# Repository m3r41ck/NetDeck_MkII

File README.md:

# Custom Macropad Project

## Project Overview
This is a custom macropad I designed, assembled, and programmed as a personal project to strengthen my hardware and embedded systems skills.

## Features
- PCB design (created using KiCad)
- Firmware flashing QMK
- Hardware assembly and soldering

## Current Status
✅ Moved from breadboard to custom PCB.  
🔜 Designing custom enclosure and expanding firmware functionality.

## Lessons Learned
- Double-check PCB traces before ordering!
- How to debug hardware connections
- How to flash and customize firmware

## Next Steps
- Design and 3D-print an enclosure
- Add support for additional macros and features

## Images

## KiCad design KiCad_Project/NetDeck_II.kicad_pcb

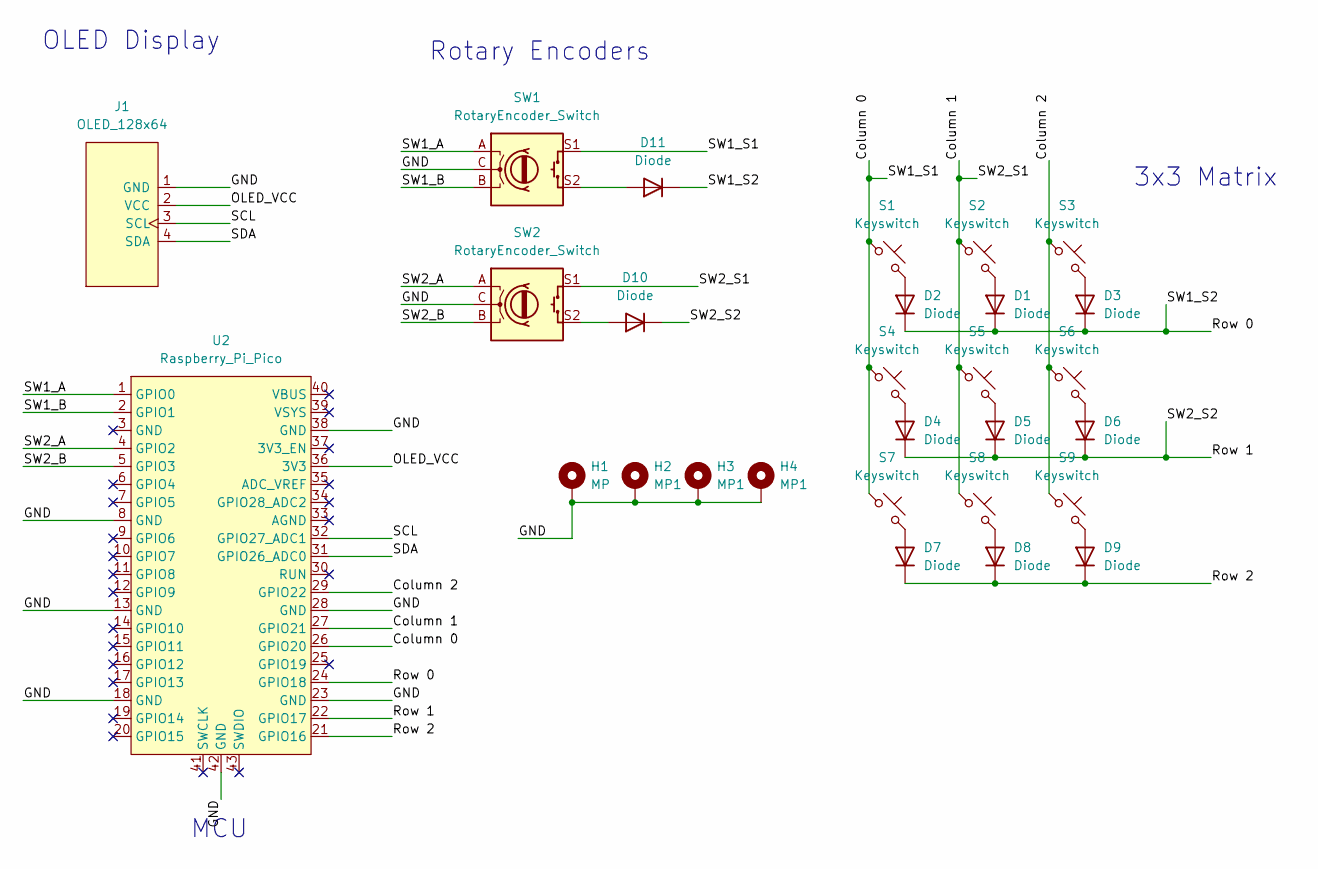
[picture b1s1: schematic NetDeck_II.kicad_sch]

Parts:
D1, D2, D3, D4, D5, D6, D7, D8, D9, D10, D11: Diode; Diode_DO-35
H1: MP; MountingHole_3.5mm_Pad_Via
H2, H3, H4: MP1; MountingHole_3.5mm_Pad_Via
J1: OLED_128x64
S1, S2, S3, S4, S5, S6, S7, S8, S9: Keyswitch; MX_PCB_1.00u
SW1, SW2: RotaryEncoder_Switch; RotaryEncoder_Alps_EC11E-Switch_Vertical_H20mm
U2: Raspberry_Pi_Pico

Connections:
/Column 0: S1.1, S4.1, S7.1, SW1.S1, U2.26 (GPIO20)
/Column 1: S2.1, S5.1, S8.1, SW2.S1, U2.27 (GPIO21)
/Column 2: S3.1, S6.1, S9.1, U2.29 (GPIO22)
/GND: H1.1, H2.1, H3.1, H4.1, J1.1 (GND), SW1.C, SW2.C, U2.8 (GND), U2.13 (GND), U2.18 (GND), U2.23 (GND), U2.28 (GND), U2.38 (GND), U2.42 (GND)
/OLED_VCC: J1.2 (VCC), U2.36 (3V3)
/Row 0: D1.1 (K), D2.1 (K), D3.1 (K), D11.1 (K), U2.24 (GPIO18)
/Row 1: D4.1 (K), D5.1 (K), D6.1 (K), D10.1 (K), U2.22 (GPIO17)
/Row 2: D7.1 (K), D8.1 (K), D9.1 (K), U2.21 (GPIO16)
/SCL: J1.3 (SCL), U2.32 (GPIO27_ADC1)
/SDA: J1.4 (SDA), U2.31 (GPIO26_ADC0)
/SW1_A: SW1.A, U2.1 (GPIO0)
/SW1_B: SW1.B, U2.2 (GPIO1)
/SW2_A: SW2.A, U2.4 (GPIO2)
/SW2_B: SW2.B, U2.5 (GPIO3)
unnamed: D1.2 (A), S2.2
unnamed: D2.2 (A), S1.2
unnamed: D3.2 (A), S3.2
unnamed: D4.2 (A), S4.2
unnamed: D5.2 (A), S5.2
unnamed: D6.2 (A), S6.2
unnamed: D7.2 (A), S7.2
unnamed: D8.2 (A), S8.2
unnamed: D9.2 (A), S9.2
unnamed: D10.2 (A), SW2.S2
unnamed: D11.2 (A), SW1.S2

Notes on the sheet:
3x3 Matrix
MCU
Rotary Encoders
OLED Display

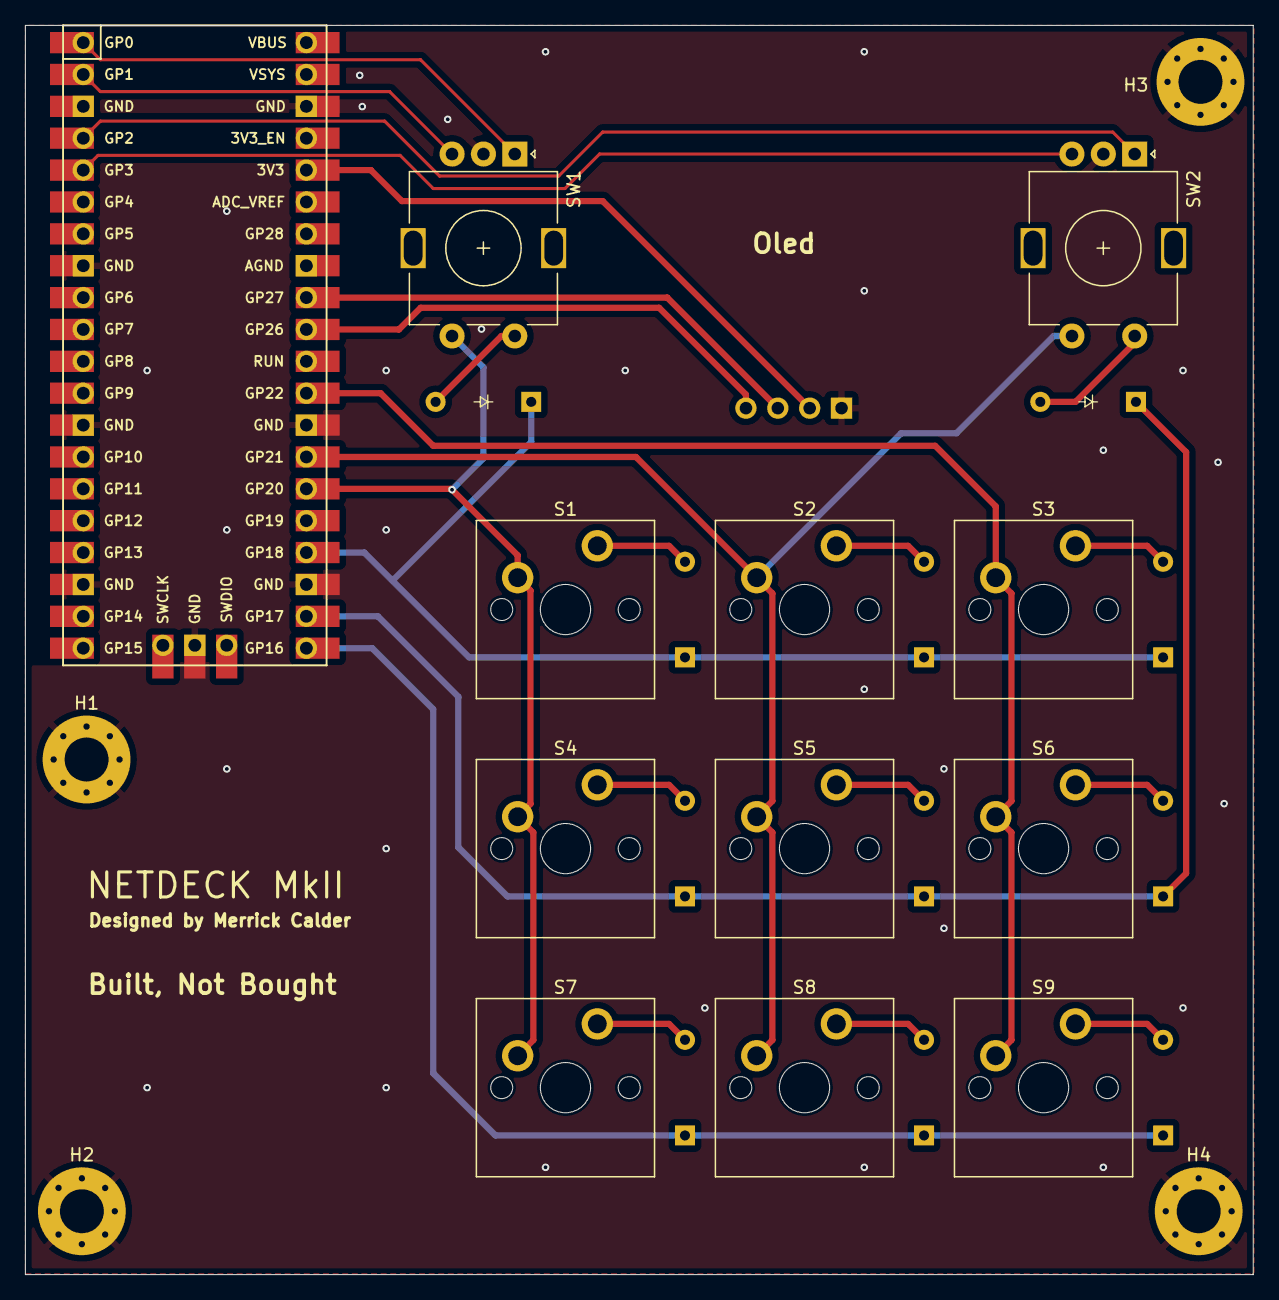
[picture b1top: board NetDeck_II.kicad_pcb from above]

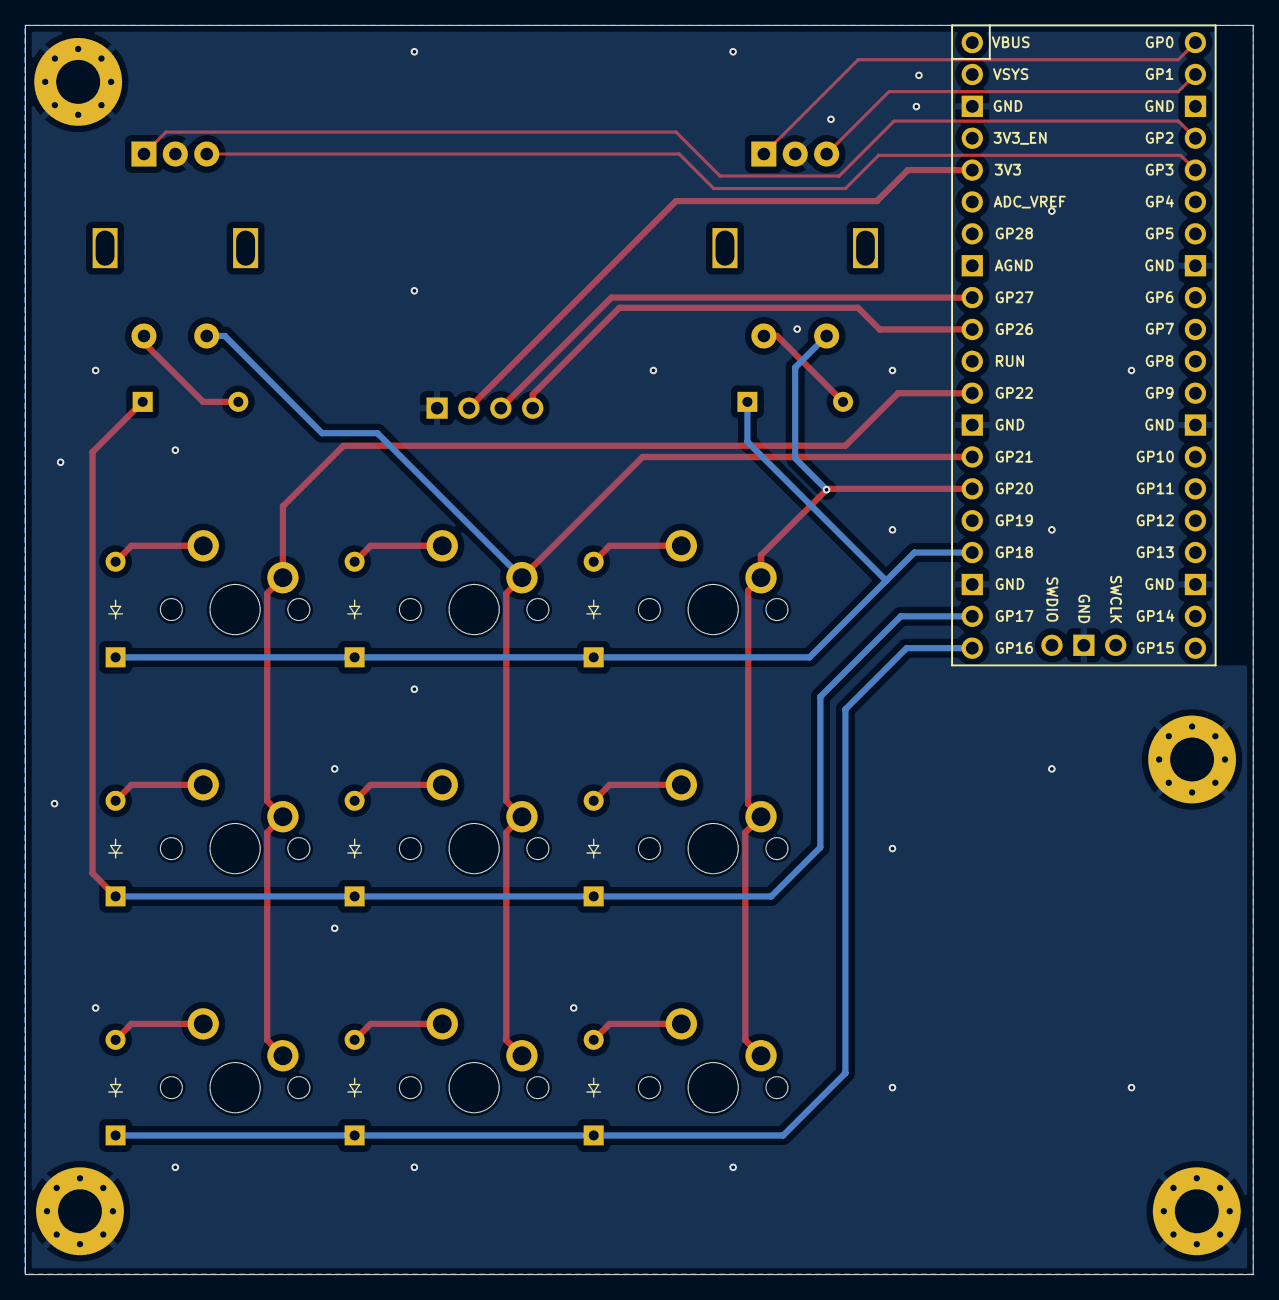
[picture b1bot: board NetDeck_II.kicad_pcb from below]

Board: 2 copper layers, 97.8 x 99.5 mm, 28 parts (9 on the bottom side), 25 nets.
